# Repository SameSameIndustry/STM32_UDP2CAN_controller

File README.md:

# w5500_UDP — STM32G431 + W5500 UDP⇄CAN エンドエフェクタ制御基板

STM32G431 + WIZnet W5500(Ethernet) を使い、PC(Python)から UDP で直接 CAN バス上のアクチュエータ
(DJI C610 ESC / TTL サーボ / 差動ワイヤ機構モータ) を制御するための、基板設計(KiCad)・ファームウェア
(STM32CubeMX + CMake)・PC側ツール一式です。

## このリポジトリの範囲

ロボットアーム全体は「GIM6010/GIM8018 で関節を駆動する基板(192.168.1.100)」と「本基板=エンド
エフェクタ基板(192.168.1.101)」の 2 枚の STM32G431+W5500 基板を同一 LAN 上で使う構成を前提にしています。
**本リポジトリに含まれるファームウェアは 192.168.1.101 側(エンドエフェクタ基板)のみ**です。
GIM 基板側のファームウェアは別ファーム・別管理であり、ここには含まれていません
(`tools/odrive_setup/` の ODrive 初期設定スクリプトや `tools/hl_control/` 内の一部スクリプトは
GIM 側の調査・設定用に書かれたものですが、GIM 基板自体のファームウェアソースはありません)。

## ディレクトリ構成

| パス | 内容 |
|---|---|
| `UDP_w5500/` | KiCad 9 基板設計データ(回路図・PCB・ガーバー・3D モデル) |
| `UDP_w5500/jlcpcb/` | JLCPCB 発注用ガーバー・BOM・CPL(エクスポート済み) |
| `G431_w5500/` | STM32G431 ファームウェア本体(CMake ビルド) |
| `tools/as5600_monitor/` | AS5600 磁気エンコーダの角度を UDP 経由で監視する CLI |
| `tools/can_id_scanner/` | 2 基板分の状態を 1 ウィンドウ(上下2セクション)で見る Tkinter GUI、CAN ID 調査用スクリプト |
| `tools/hl_control/` | 高レベル制御 UDP プロトコルの実装・診断スクリプト、ROS2 連携 GUI |
| `tools/odrive_setup/` | ODrive ベースの GIM6010-8/GIM8108-8 を USB 経由で初期設定・較正するスクリプト(本基板のファームとは独立) |
| `CAN_PROTOCOL_*.md` | CAN バス上の各デバイスのフレーム仕様書 |
| `tools/hl_control/PROTOCOL_HL_CONTROL_UDP.md` | 高レベル制御 UDP プロトコル仕様書 |
| `ref/` | 使用部品(モータ・エンコーダ等)のデータシート・メーカー資料(参考資料) |
| `parts/` | KiCad 用の追加シンボル/フットプリント/3D モデルライブラリ |

## ハードウェア概要

- MCU: STM32G431CBT6 (Cortex-M4F)
- Ethernet: WIZnet **W5500**(SPI 接続、静的 IP)
- CAN: FDCAN1, **1 Mbps classic CAN**, 標準 11bit ID
- バス上のデバイスと CAN ID:

  | デバイス | CAN ID | 通信方向 | 仕様書 |
  |---|---|---|---|
  | DJI C610 (M2006 用 ESC) | `0x01`(ESC ID=1) + AS5600 フィードバック | 送受信 | — (DJI 標準プロトコル) |
  | TTL サーボ基板 | `0x21` | 受信専用(本基板からは送信しない) | [`CAN_PROTOCOL_TTL-SERVO.md`](CAN_PROTOCOL_TTL-SERVO.md) |
  | 差動ワイヤ機構モータ(ピッチ/ヨー) | `0x11` / `0x12` | 受信専用(本基板からは送信しない) | [`CAN_PROTOCOL_wave_motor.md`](CAN_PROTOCOL_wave_motor.md) |

- 3D モデル: `UDP_w5500/3D/UDP_w5500.step` が基板単体の統合 STEP。`3D_base*.ipt/.stl` /
  `3D_clear*.ipt/.stl` はエンクロージャ部品(Autodesk Inventor 形式 + 変換済み STL)。
  - 既知の注意点: PCB 上の RJ45 コネクタの 3D モデル参照(`${KIPRJMOD}/EASYEDA_MODELS/RJ45-TH_HR911105A.step`)
    は本リポジトリに含まれていません。KiCad の 3D ビューアでその部品だけ表示されませんが、
    回路設計・ガーバー出力には影響しません。

## ビルド環境

- [Arm GNU Toolchain](https://developer.arm.com/downloads/-/arm-gnu-toolchain-downloads)
  (`arm-none-eabi-gcc` 等) を PATH に追加
- CMake 3.22 以上、Ninja
- STM32CubeMX (`G431_w5500/G431_w5500.ioc` を編集・再生成する場合のみ)
- フラッシュ/デバッグ用に ST-Link デバッグプローブ + [OpenOCD](https://openocd.org/) 、
  または STM32CubeProgrammer

### CLI でビルド

```sh
cd G431_w5500
cmake --preset Debug
cmake --build --preset Debug
```

### VS Code でビルド/フラッシュ

本リポジトリには `.vscode/` 設定を同梱しています。

1. `.vscode/settings.json` の `cortex-debug.openocdPath`、`.vscode/tasks.json` の
   `Flash` タスクの `command` は `"openocd"` としてあります。OpenOCD を PATH に追加するか、
   お使いの環境のインストール先の絶対パスに書き換えてください。
2. `.vscode/c_cpp_properties.json` の `compilerPath` は Arm GNU Toolchain の Windows
   インストーラのデフォルト位置を指しています。インストール先が異なる場合は書き換えてください。
3. ビルド: `Ctrl+Shift+B` (`Build Debug` タスク、`cmake --build` を実行)
4. 書き込み: タスク `Flash` (`Build Debug` に依存、OpenOCD + ST-Link で書き込み・検証・リセット)
5. デバッグ: 実行とデバッグ → `Debug (OpenOCD)`

## ネットワーク設定(環境ごとに書き換えが必要)

基板の IP/MAC と、ブロードキャスト以外の送信先 PC の IP アドレスは
[`G431_w5500/Core/Src/main.c`](G431_w5500/Core/Src/main.c) 内にコンパイル時定数として直接
記述されています。**自分の環境の LAN 構成に合わせて書き換えてから書き込んでください。**

```c
.mac = {0x00, 0x08, 0xdc, 0x11, 0x22, 0x65},
.ip  = {192, 168, 1, 101},   // 本基板(エンドエフェクタ)の固定IP
.sn  = {255, 255, 255, 0},
.gw  = {192, 168, 1, 1},

uint8_t dest_ip[4] = {192, 168, 1, 2}; // ← PC側のIPアドレスに書き換える
```

GIM 基板(別ファーム)を同一 LAN に併設する場合は、IP(`192.168.1.100` 等)と MAC が重複しないように
してください。

### UDP ポート一覧

| ポート | 方向 | 用途 |
|---|---|---|
| 5000 | STM32→PC | 定期 "Hello" デモ送信(`dest_ip` 宛) |
| 5001 | PC↔STM32 | 生 CAN フレーム中継(CAN ID 調査・デバッグ用)。PC から 1 回何か送ると以後は受信した全 CAN フレームが転送される |
| 5002 | STM32→PC(broadcast) | ハートビート(定期送信、`255.255.255.255` 宛) |
| 5003 | PC→STM32(単方向) | 高レベル制御 UDP(TTL サーボ/wave motor/C610 を直接操作、詳細は [`PROTOCOL_HL_CONTROL_UDP.md`](tools/hl_control/PROTOCOL_HL_CONTROL_UDP.md)) |
| 5004 | STM32→PC | AS5600 角度モニタ(ストリーム配信) |
| 8888 | PC(ROS2)→STM32 | ROS2 連携プロトコル受信 |
| 8889 | STM32→PC(ROS2) | ROS2 連携プロトコル フィードバック送信 |

## PC 側ツール(Python)

Python 3.x、標準ライブラリ(`socket` / `struct` / `tkinter` / `argparse`)のみで動作します
(`tkinter` を使う GUI ツールは Tcl/Tk 入りの Python が必要)。`tools/odrive_setup/` の
スクリプトのみ追加で ODrive 公式ライブラリが必要です。

```sh
pip install odrive   # tools/odrive_setup/ のスクリプトを使う場合のみ
```

主なツール:

- `tools/can_id_scanner/can_id_scanner.py` — GIM 基板(100)とエンドエフェクタ基板(101)の
  両方を 1 ウィンドウ(上下2セクション)で扱う GUI。生 CAN フレーム(ポート5001)の送受信・デコード。
- `tools/hl_control/ros2_arm_control.py` — 同様の 2 基板 GUI(ROS2/sharmech プロトコル版、ポート8888/8889)。
- `tools/as5600_monitor/as5600_monitor.py` — AS5600 角度モニタ(ポート5004)の CLI クライアント。
- `tools/hl_control/diagnose_gim_axes.py` / `ramp_gim6010_pitch.py` — GIM 基板側の
  ODrive heartbeat 診断・角度ランプ送信(ポート5001 の生 CAN ブリッジ経由、GIM 基板向け)。
- `tools/odrive_setup/odrive_configure.py` / `odrive_inspect.py` 等 — USB 接続した
  ODrive(GIM6010-8/GIM8108-8)の初期設定・読み取り専用確認スクリプト。

いずれも `-h` / `--help` で使用法を確認できます。

## 基板発注

`UDP_w5500/jlcpcb/production_files/` に JLCPCB 向けの BOM・CPL・ガーバー一式(zip)が、
`UDP_w5500/jlcpcb/gerber/` に展開済みガーバー/ドリルデータがあります。他の基板製造業者を使う場合は
`UDP_w5500/UDP_w5500.kicad_pcb` から KiCad 9 でガーバーを再出力してください。

## 既知の制限・未解決事項

- RJ45 コネクタの 3D モデル参照が欠落している(上記参照)。電気的な設計・発注には影響しない。
- `tools/hl_control/ros2_arm_control.py` はワイヤフォーマットの仕様根拠として社内リポジトリ
  `sharmech`(非公開・本リポジトリには含まれない)の文書を参照しているコメントがありますが、
  スクリプト自体は標準ライブラリのみで完結しており、`sharmech` が無くても動作します。

## ライセンス

[MIT License](LICENSE)。ただし `G431_w5500/Core/Drivers/W5500/`(WIZnet ioLibrary)、
`G431_w5500/Drivers/CMSIS/`、`G431_w5500/Drivers/STM32G4xx_HAL_Driver/` は各ディレクトリ・
ファイルヘッダに記載された元のライセンス(WIZnet license / Apache-2.0 / BSD-3-Clause)に従います。

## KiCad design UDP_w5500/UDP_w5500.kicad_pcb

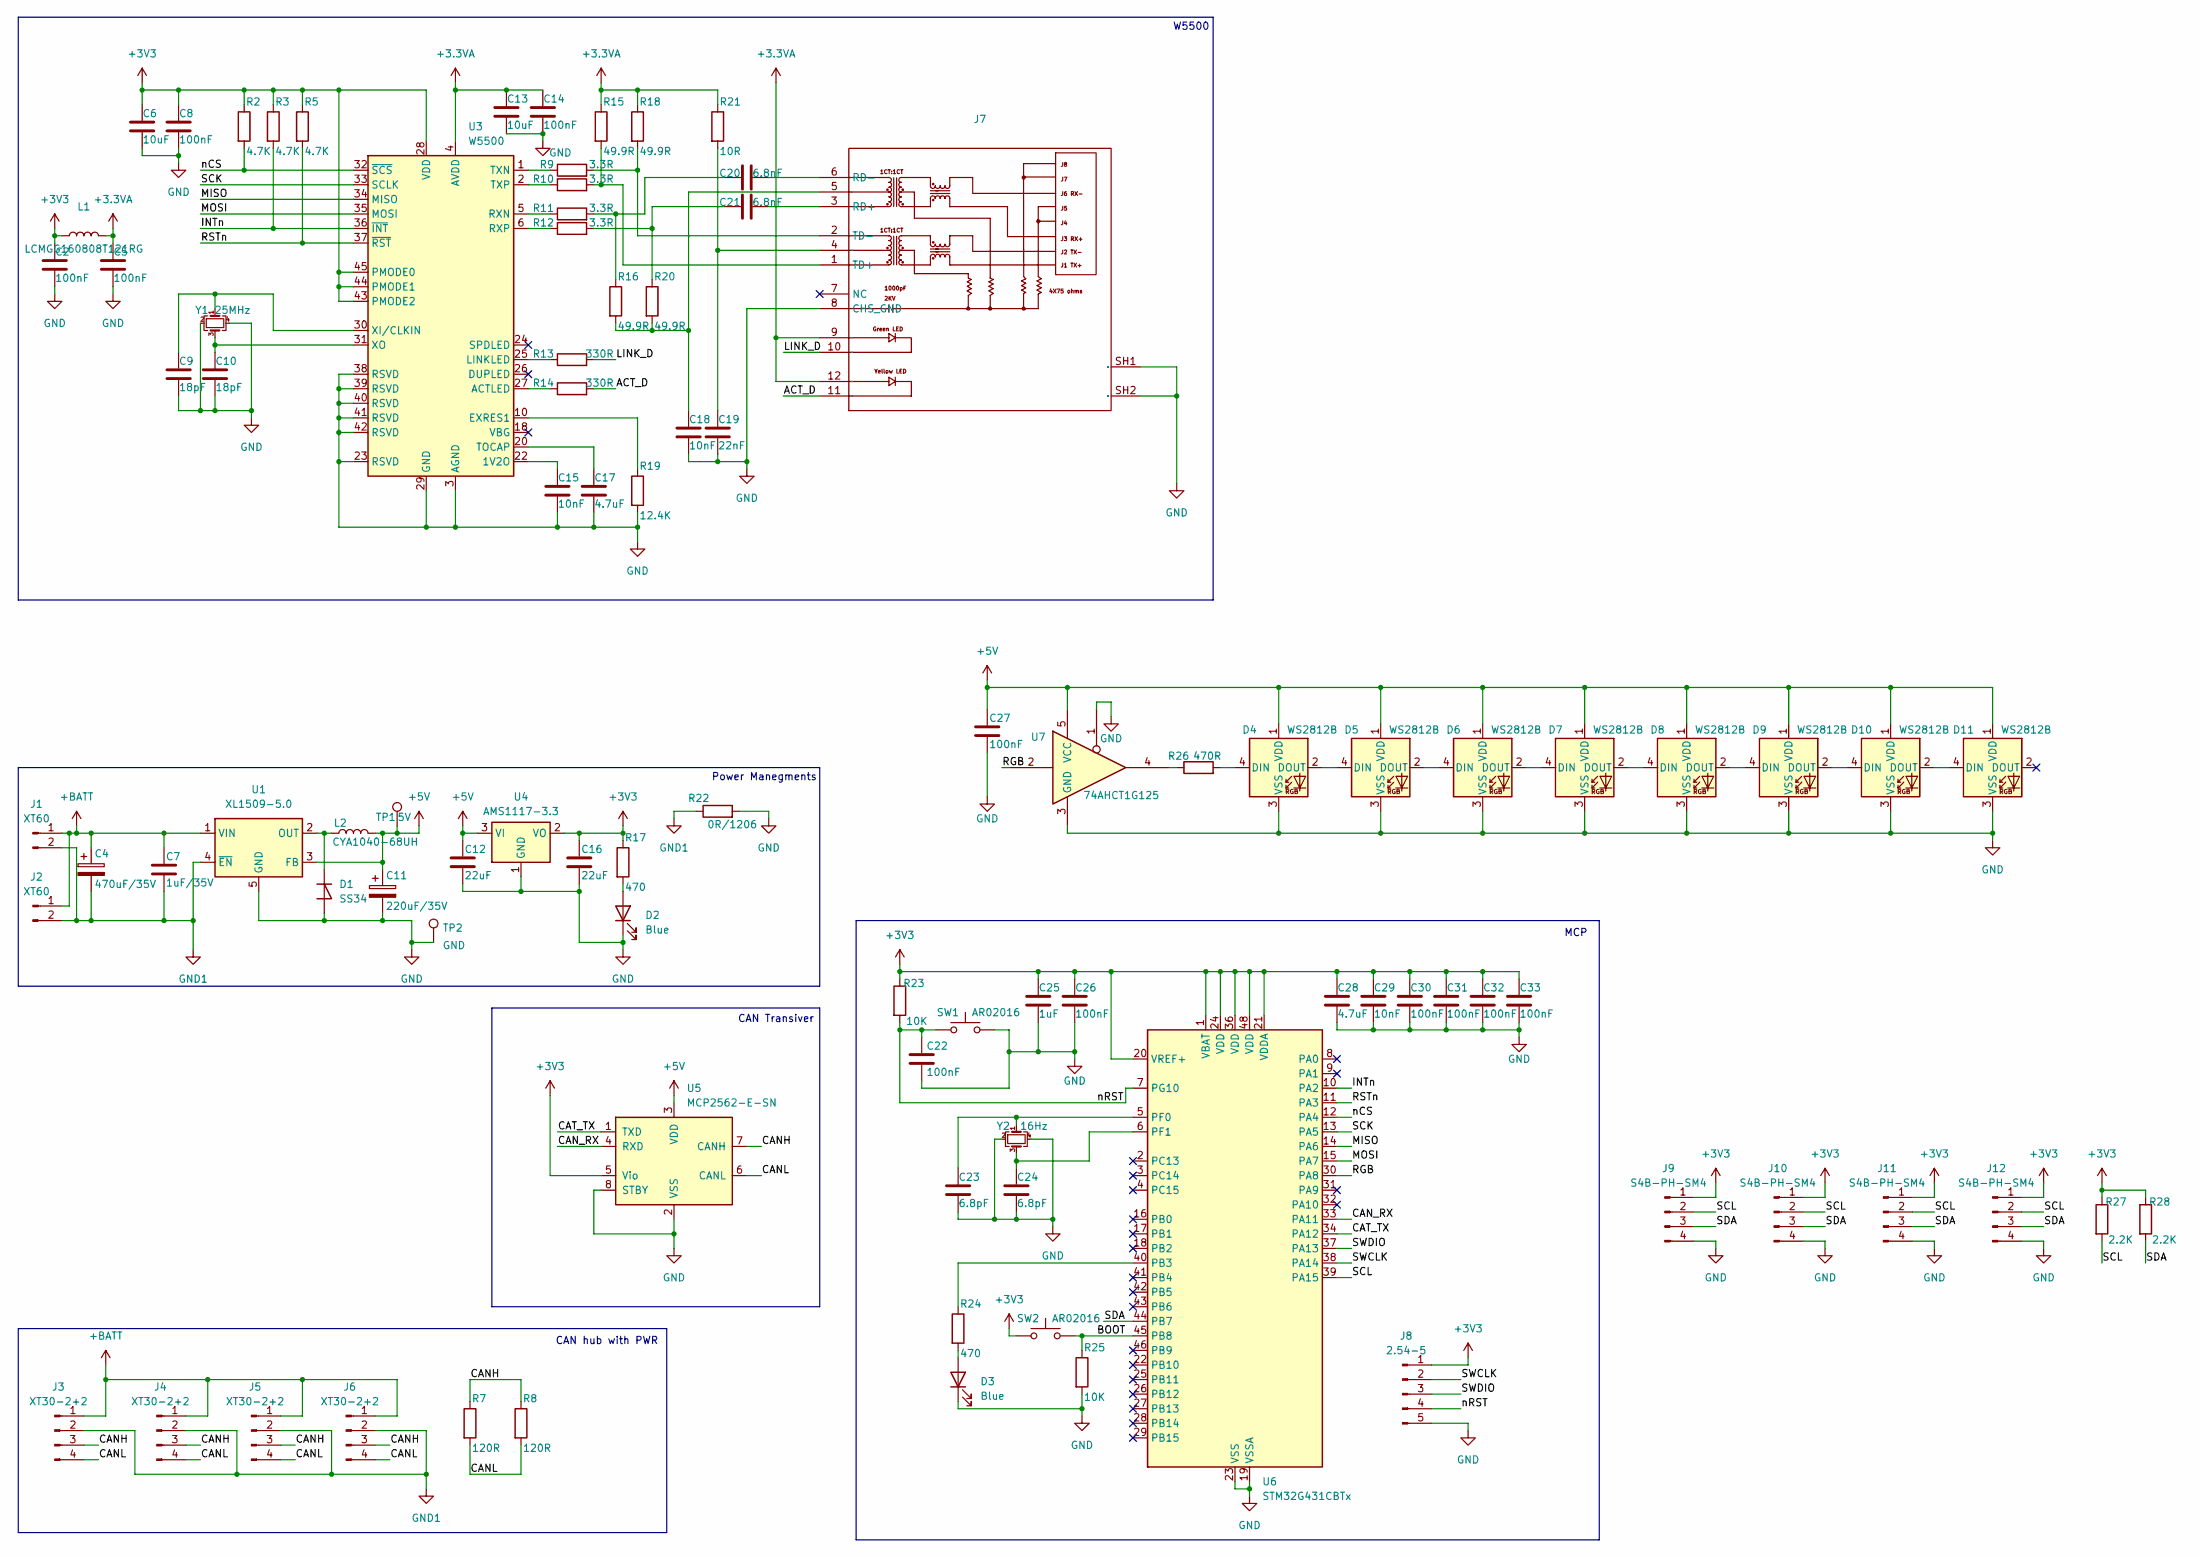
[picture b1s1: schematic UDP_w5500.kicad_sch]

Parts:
C2, C5, C8, C14, C22, C26, C27, C30, C31, C32, C33: 100nF; C_0603_1608Metric_Pad1.08x0.95mm_HandSolder; LCSC C14663
C4: 470uF/35V; CP_Radial_D10.0mm_P5.00mm
C6, C13: 10uF; C_0603_1608Metric_Pad1.08x0.95mm_HandSolder; LCSC C19702
C7: 1uF/35V; C_0603_1608Metric_Pad1.08x0.95mm_HandSolder; LCSC C15849
C9, C10: 18pF; C_0603_1608Metric_Pad1.08x0.95mm_HandSolder; LCSC C1647
C11: 220uF/35V; CP_Radial_D8.0mm_P3.50mm
C12, C16: 22uF; C_0603_1608Metric_Pad1.08x0.95mm_HandSolder; LCSC C59461
C15, C18, C29: 10nF; C_0603_1608Metric_Pad1.08x0.95mm_HandSolder; LCSC C57112
C17, C28: 4.7uF; C_0603_1608Metric_Pad1.08x0.95mm_HandSolder; LCSC C19666
C19: 22nF; C_0603_1608Metric_Pad1.08x0.95mm_HandSolder; LCSC C21122
C20, C21: 6.8nF; C_0603_1608Metric_Pad1.08x0.95mm_HandSolder; LCSC C1631
C23, C24: 6.8pF; C_0603_1608Metric_Pad1.08x0.95mm_HandSolder; LCSC C1679
C25: 1uF; C_0603_1608Metric_Pad1.08x0.95mm_HandSolder; LCSC C15849
D1: SS34; D_SMA; LCSC C8678
D2, D3: Blue; LED_0603_1608Metric_Pad1.05x0.95mm_HandSolder; LCSC C7012319
D4, D5, D6, D7, D8, D9, D10, D11: WS2812B; LED_WS2812B_PLCC4_5.0x5.0mm_P3.2mm
J1: XT60; AMASS_XT60IPW-M_1x03_P7.20mm_Horizontal
J2: XT60; AMASS_XT60PW-F_1x02_P7.20mm_Horizontal
J3, J4, J5, J6: XT30-2+2; CONN-TH_4P-XT30PW-M
J7: RJ45-TH_HR911105A; Manufacturer Part HR911105A; LCSC Part Name 弯插 带LED
J8: 2.54-5; PinHeader_1x05_P2.54mm_Vertical
J9, J10, J11, J12: S4B-PH-SM4; JST_PH_S4B-PH-SM4-TB_1x04-1MP_P2.00mm_Horizontal; LCSC C265102
L1: LCMGG160808T121RG; L_0603_1608Metric; LCSC C14709
L2: CYA1040-68UH; IND-SMD_L11.6-W10.1; LCSC C6364682
R2, R3, R5: 4.7K; R_0603_1608Metric_Pad0.98x0.95mm_HandSolder; LCSC C23162
R7, R8: 120R; R_0603_1608Metric_Pad0.98x0.95mm_HandSolder; LCSC C22787
R9, R10, R11, R12: 3.3R; R_0603_1608Metric_Pad0.98x0.95mm_HandSolder; LCSC C22979
R13, R14: 330R; R_0603_1608Metric_Pad0.98x0.95mm_HandSolder; LCSC C23138
R15, R16, R18, R20: 49.9R; R_0603_1608Metric_Pad0.98x0.95mm_HandSolder; LCSC C23185
R17, R24: 470; R_0603_1608Metric_Pad0.98x0.95mm_HandSolder; LCSC C23179
R19: 12.4K; R_0603_1608Metric_Pad0.98x0.95mm_HandSolder; LCSC C22865
R21: 10R; R_0603_1608Metric_Pad0.98x0.95mm_HandSolder; LCSC C22859
R22: 0R/1206; R_1206_3216Metric; LCSC C22356801
R23, R25: 10K; R_0603_1608Metric_Pad0.98x0.95mm_HandSolder; LCSC C25804
R26: 470R; R_0603_1608Metric_Pad0.98x0.95mm_HandSolder; LCSC C23179
R27, R28: 2.2K; R_0603_1608Metric_Pad0.98x0.95mm_HandSolder; LCSC C4190
SW1, SW2: AR02016; SW-SMD_L3.9-W3.0-P4.45; LCSC C720477
TP1: 5V; TestPoint_Pad_D3.0mm
TP2: GND; TestPoint_Pad_D3.0mm
U1: XL1509-5.0; SOIC-8_3.9x4.9mm_P1.27mm; LCSC C2902368
U3: W5500; LQFP-48_7x7mm_P0.5mm; LCSC C32843
U4: AMS1117-3.3; SOT-223-3_TabPin2; LCSC C6186
U5: MCP2562-E-SN; SOIC-8_3.9x4.9mm_P1.27mm; LCSC C53609
U6: STM32G431CBTx; LQFP-48_7x7mm_P0.5mm; LCSC C529355
U7: 74AHCT1G125; SOT-23-5_HandSoldering; LCSC C20617900
Y1: 25MHz; Crystal_SMD_3225-4Pin_3.2x2.5mm; LCSC C9006
Y2: 16Hz; Crystal_SMD_3225-4Pin_3.2x2.5mm; LCSC C13738

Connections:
+3.3VA: C5.1, C13.1, C14.1, J7.9, J7.12, L1.2, R15.1, R18.1, R21.1, U3.4 (AVDD), U3.8 (AVDD), U3.11 (AVDD), U3.15 (AVDD), U3.17 (AVDD), U3.21 (AVDD)
+3V3: C2.1, C6.1, C8.1, C16.1, C25.1, C26.1, C28.1, C29.1, C30.1, C31.1, C32.1, C33.1, J8.1, J9.1, J10.1, J11.1, J12.1, L1.1, R2.1, R3.1, R5.1, R17.1, R23.1, R27.1, R28.1, SW2.1, U3.28 (VDD), U3.43 (PMODE2), U3.44 (PMODE1), U3.45 (PMODE0), U4.2 (VO), U5.5 (Vio), U6.1 (VBAT), U6.20 (VREF+), U6.21 (VDDA), U6.24 (VDD), U6.36 (VDD), U6.48 (VDD)
+5V: C11.1, C12.1, C27.1, D4.1 (VDD), D5.1 (VDD), D6.1 (VDD), D7.1 (VDD), D8.1 (VDD), D9.1 (VDD), D10.1 (VDD), D11.1 (VDD), L2.2, TP1.1, U1.3 (FB), U4.3 (VI), U5.3 (VDD), U7.5 (VCC)
+BATT: C4.1, C7.1, J1.1, J2.1, J3.1, J4.1, J5.1, J6.1, U1.1 (VIN)
/ACT_D: J7.11, R14.2
/BOOT: R25.1, SW2.2, U6.45 (PB8)
/CANH: J3.3, J4.3, J5.3, J6.3, R7.1, R8.1, U5.7 (CANH)
/CANL: J3.4, J4.4, J5.4, J6.4, R7.2, R8.2, U5.6 (CANL)
/CAN_RX: U5.4 (RXD), U6.33 (PA11)
/CAT_TX: U5.1 (TXD), U6.34 (PA12)
/INTn: R3.2, U3.36 (~INT), U6.10 (PA2)
/LINK_D: J7.10, R13.2
/MISO: U3.34 (MISO), U6.14 (PA6)
/MOSI: U3.35 (MOSI), U6.15 (PA7)
/RGB: U6.30 (PA8), U7.2
/RSTn: R5.2, U3.37 (~RST), U6.11 (PA3)
/SCK: U3.33 (SCLK), U6.13 (PA5)
/SCL: J9.2, J10.2, J11.2, J12.2, R27.2, U6.39 (PA15)
/SDA: J9.3, J10.3, J11.3, J12.3, R28.2, U6.44 (PB7)
/SWCLK: J8.2, U6.38 (PA14)
/SWDIO: J8.3, U6.37 (PA13)
/nCS: R2.2, U3.32 (~SCS), U6.12 (PA4)
/nRST: C22.1, J8.4, R23.2, SW1.1, U6.7 (PG10)
GND: C2.2, C5.2, C6.2, C8.2, C9.2, C10.2, C11.2, C12.2, C13.2, C14.2, C15.2, C16.2, C17.2, C18.2, C19.2, C22.2, C23.2, C24.2, C25.2, C26.2, C27.2, C28.2, C29.2, C30.2, C31.2, C32.2, C33.2, D1.2 (A), D2.1 (K), D3.1 (K), D4.3 (VSS), D5.3 (VSS), D6.3 (VSS), D7.3 (VSS), D8.3 (VSS), D9.3 (VSS), D10.3 (VSS), D11.3 (VSS), J7.8 (CHS_GND), J7.SH1, J7.SH2, J8.5, J9.4, J10.4, J11.4, J12.4, R19.2, R22.2, R25.2, SW1.2, TP2.1, U1.5 (GND), U1.6 (GND), U1.7 (GND), U1.8 (GND), U3.3 (AGND), U3.9 (AGND), U3.14 (AGND), U3.16 (AGND), U3.19 (AGND), U3.23 (RSVD), U3.29 (GND), U3.38 (RSVD), U3.39 (RSVD), U3.40 (RSVD), U3.41 (RSVD), U3.42 (RSVD), U3.48 (AGND), U4.1 (GND), U5.2 (VSS), U5.8 (STBY), U6.19 (VSSA), U6.23 (VSS), U6.35 (VSS), U6.47 (VSS), U7.1, U7.3 (GND), Y1.2, Y1.4, Y2.2, Y2.4
GND1: C4.2, C7.2, J1.2, J2.2, J3.2, J4.2, J5.2, J6.2, R22.1, U1.4 (~EN)
unnamed: C18.1, J7.5, R16.2, R20.2
unnamed: C19.1, J7.4, R21.2
unnamed: C20.1, R11.2, R16.1
unnamed: C21.1, R12.2, R20.1
unnamed: D1.1 (K), L2.1, U1.2 (OUT)
unnamed: D2.2 (A), R17.2
unnamed: D3.2 (A), R24.2
unnamed: D4.4 (DIN), R26.2
unnamed: D4.2 (DOUT), D5.4 (DIN)
unnamed: D5.2 (DOUT), D6.4 (DIN)
unnamed: D6.2 (DOUT), D7.4 (DIN)
unnamed: D7.2 (DOUT), D8.4 (DIN)
unnamed: D8.2 (DOUT), D9.4 (DIN)
unnamed: D9.2 (DOUT), D10.4 (DIN)
unnamed: D10.2 (DOUT), D11.4 (DIN)
unnamed: C21.2, J7.3 (RD+)
unnamed: C20.2, J7.6 (RD-)
unnamed: J7.1 (TD+), R10.2, R15.2
unnamed: J7.2 (TD-), R9.2, R18.2
unnamed: R26.1, U7.4
unnamed: C15.1, U3.22 (1V2O)
unnamed: R14.1, U3.27 (ACTLED)
unnamed: R19.1, U3.10 (EXRES1)
unnamed: R13.1, U3.25 (LINKLED)
unnamed: R11.1, U3.5 (RXN)
unnamed: R12.1, U3.6 (RXP)
unnamed: C17.1, U3.20 (TOCAP)
unnamed: R9.1, U3.1 (TXN)
unnamed: R10.1, U3.2 (TXP)
unnamed: C9.1, U3.30 (XI/CLKIN), Y1.1
unnamed: C10.1, U3.31 (XO), Y1.3
unnamed: R24.1, U6.40 (PB3)
unnamed: C23.1, U6.5 (PF0), Y2.1
unnamed: C24.1, U6.6 (PF1), Y2.3

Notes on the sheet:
CAN hub with PWR
MCP
W5500
Power Manegments
CAN Transiver

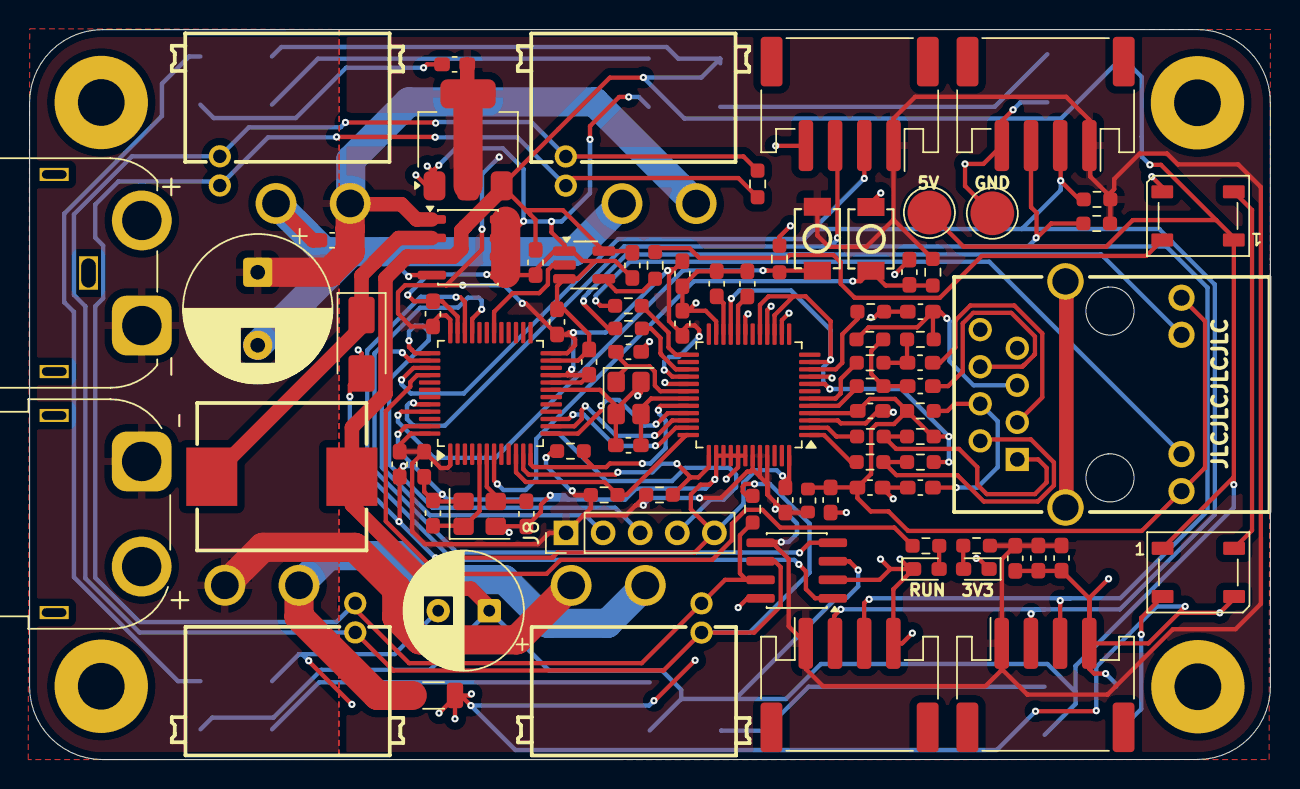
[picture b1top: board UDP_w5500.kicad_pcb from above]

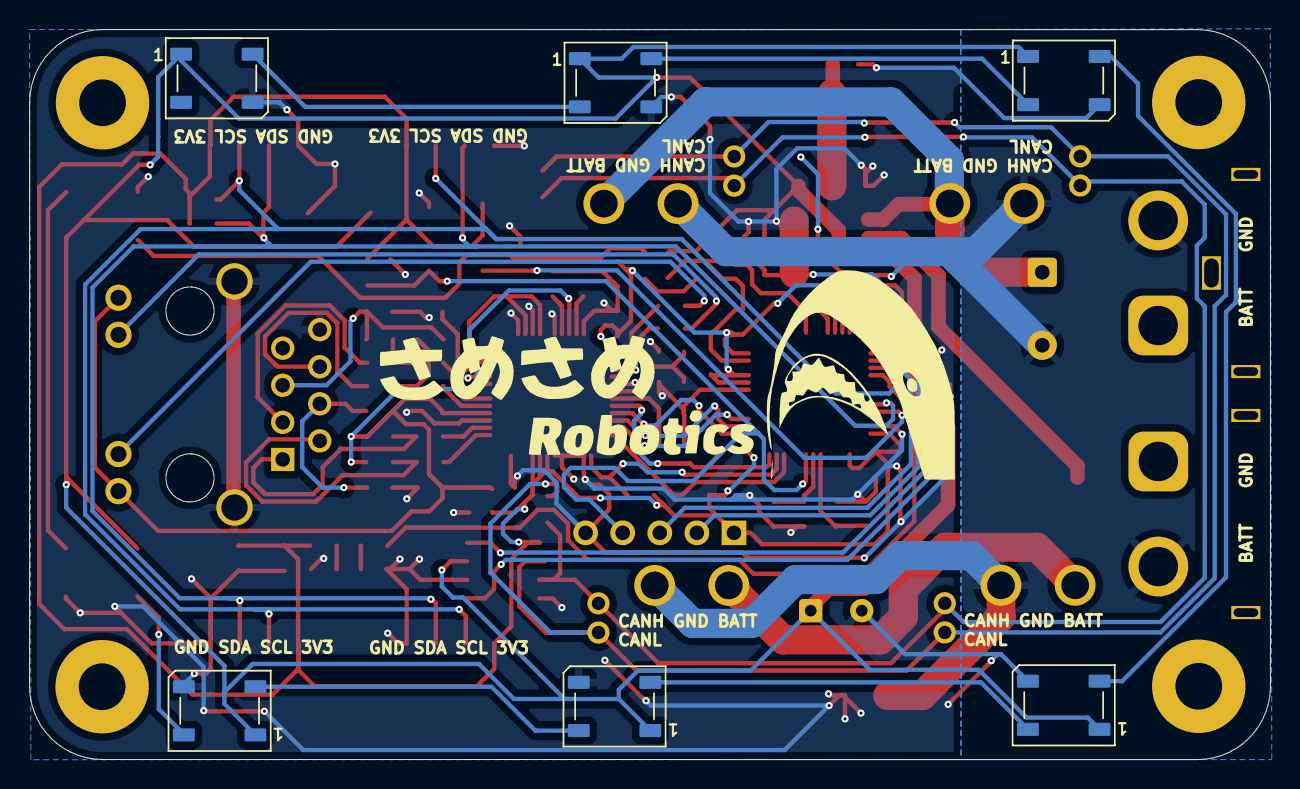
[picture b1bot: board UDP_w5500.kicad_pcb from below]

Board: 2 copper layers, 85.0 x 50.0 mm, 93 parts (6 on the bottom side), 59 nets.

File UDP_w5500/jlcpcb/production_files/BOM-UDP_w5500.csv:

Comment,Designator,Footprint,LCSC,Quantity
0R/1206,R22,R_1206_3216Metric,C22356801,1
100nF,"C14,C2,C22,C26,C27,C30,C31,C32,C33,C5,C8",C_0603_1608Metric_Pad1.08x0.95mm_HandSolder,C14663,11
10K,"R23,R25",R_0603_1608Metric_Pad0.98x0.95mm_HandSolder,C25804,2
10R,R21,R_0603_1608Metric_Pad0.98x0.95mm_HandSolder,C22859,1
10nF,"C15,C18,C29",C_0603_1608Metric_Pad1.08x0.95mm_HandSolder,C57112,3
10uF,"C13,C6",C_0603_1608Metric_Pad1.08x0.95mm_HandSolder,C19702,2
12.4K,R19,R_0603_1608Metric_Pad0.98x0.95mm_HandSolder,C22865,1
120R,"R7,R8",R_0603_1608Metric_Pad0.98x0.95mm_HandSolder,C22787,2
16Hz,Y2,Crystal_SMD_3225-4Pin_3.2x2.5mm,C13738,1
18pF,"C10,C9",C_0603_1608Metric_Pad1.08x0.95mm_HandSolder,C1647,2
1uF,C25,C_0603_1608Metric_Pad1.08x0.95mm_HandSolder,C15849,1
1uF/35V,C7,C_0603_1608Metric_Pad1.08x0.95mm_HandSolder,C15849,1
2.2K,"R27,R28",R_0603_1608Metric_Pad0.98x0.95mm_HandSolder,C4190,2
22nF,C19,C_0603_1608Metric_Pad1.08x0.95mm_HandSolder,C21122,1
22uF,"C12,C16",C_0603_1608Metric_Pad1.08x0.95mm_HandSolder,C59461,2
25MHz,Y1,Crystal_SMD_3225-4Pin_3.2x2.5mm,C9006,1
3.3R,"R10,R11,R12,R9",R_0603_1608Metric_Pad0.98x0.95mm_HandSolder,C22979,4
330R,"R13,R14",R_0603_1608Metric_Pad0.98x0.95mm_HandSolder,C23138,2
4.7K,"R2,R3,R5",R_0603_1608Metric_Pad0.98x0.95mm_HandSolder,C23162,3
4.7uF,"C17,C28",C_0603_1608Metric_Pad1.08x0.95mm_HandSolder,C19666,2
470,"R17,R24",R_0603_1608Metric_Pad0.98x0.95mm_HandSolder,C23179,2
470R,R26,R_0603_1608Metric_Pad0.98x0.95mm_HandSolder,C23179,1
49.9R,"R15,R16,R18,R20",R_0603_1608Metric_Pad0.98x0.95mm_HandSolder,C23185,4
6.8nF,"C20,C21",C_0603_1608Metric_Pad1.08x0.95mm_HandSolder,C1631,2
6.8pF,"C23,C24",C_0603_1608Metric_Pad1.08x0.95mm_HandSolder,C1679,2
74AHCT1G125,U7,SOT-23-5_HandSoldering,C20617900,1
AMS1117-3.3,U4,SOT-223-3_TabPin2,C6186,1
AR02016,"SW1,SW2",SW-SMD_L3.9-W3.0-P4.45,C720477,2
Blue,"D2,D3",LED_0603_1608Metric_Pad1.05x0.95mm_HandSolder,C7012319,2
CYA1040-68UH,L2,IND-SMD_L11.6-W10.1,C6364682,1
LCMGG160808T121RG,L1,L_0603_1608Metric,C14709,1
MCP2562-E-SN,U5,SOIC-8_3.9x4.9mm_P1.27mm,C53609,1
S4B-PH-SM4,"J10,J11,J12,J9",JST_PH_S4B-PH-SM4-TB_1x04-1MP_P2.00mm_Horizontal,C265102,4
SS34,D1,D_SMA,C8678,1
STM32G431CBTx,U6,LQFP-48_7x7mm_P0.5mm,C529355,1
W5500,U3,LQFP-48_7x7mm_P0.5mm,C32843,1
XL1509-5.0,U1,SOIC-8_3.9x4.9mm_P1.27mm,C2902368,1
XT30-2+2,J3,CONN-TH_4P-XT30PW-M,,1
XT60,J1,AMASS_XT60IPW-M_1x03_P7.20mm_Horizontal,,1
470uF/35V,C4,CP_Radial_D10.0mm_P5.00mm,,1
XT60,J2,AMASS_XT60PW-F_1x02_P7.20mm_Horizontal,,1
XT30-2+2,J4,CONN-TH_4P-XT30PW-M,,1
XT30-2+2,J5,CONN-TH_4P-XT30PW-M,,1
~,J7,RJ45-TH_HR911105A,,1
XT30-2+2,J6,CONN-TH_4P-XT30PW-M,,1
WS2812B,D4,LED_WS2812B_PLCC4_5.0x5.0mm_P3.2mm,,1
GND,TP2,TestPoint_Pad_D3.0mm,,1
2.54-5,J8,PinHeader_1x05_P2.54mm_Vertical,,1
5V,TP1,TestPoint_Pad_D3.0mm,,1
WS2812B,D5,LED_WS2812B_PLCC4_5.0x5.0mm_P3.2mm,,1
220uF/35V,C11,CP_Radial_D8.0mm_P3.50mm,,1
WS2812B,D8,LED_WS2812B_PLCC4_5.0x5.0mm_P3.2mm,,1
WS2812B,D11,LED_WS2812B_PLCC4_5.0x5.0mm_P3.2mm,,1
WS2812B,D6,LED_WS2812B_PLCC4_5.0x5.0mm_P3.2mm,,1
WS2812B,D9,LED_WS2812B_PLCC4_5.0x5.0mm_P3.2mm,,1
WS2812B,D10,LED_WS2812B_PLCC4_5.0x5.0mm_P3.2mm,,1
WS2812B,D7,LED_WS2812B_PLCC4_5.0x5.0mm_P3.2mm,,1

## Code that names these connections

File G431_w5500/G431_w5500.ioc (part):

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Mcu.Name=STM32G431C(6-8-B)Tx
Mcu.Package=LQFP48
Mcu.UserName=STM32G431CBTx
PA11.Mode=FDCAN_Activate
PA11.Signal=FDCAN1_RX
PA12.Mode=FDCAN_Activate
PA12.Signal=FDCAN1_TX
PA13.Mode=Serial_Wire
PA13.Signal=SYS_JTMS-SWDIO
PA14.Mode=Serial_Wire
PA14.Signal=SYS_JTCK-SWCLK
PA2.Signal=GPIO_Input
PA3.Signal=GPIO_Output
PA4.Signal=GPIO_Output
PA5.Mode=Full_Duplex_Master
PA5.Signal=SPI1_SCK
PA6.Mode=Full_Duplex_Master
PA6.Signal=SPI1_MISO
PA7.Mode=Full_Duplex_Master
PA7.Signal=SPI1_MOSI
PA8.Signal=S_TIM1_CH1
PB3.Signal=GPIO_Output
PF0-OSC_IN.Mode=HSE-External-Oscillator
PF0-OSC_IN.Signal=RCC_OSC_IN
PF1-OSC_OUT.Mode=HSE-External-Oscillator
PF1-OSC_OUT.Signal=RCC_OSC_OUT
RCC.HSE_VALUE=16000000
RCC.SYSCLKFreq_VALUE=48000000
RCC.SYSCLKSource=RCC_SYSCLKSOURCE_PLLCLK
board=custom

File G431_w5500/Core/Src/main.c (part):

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  // C610Current_Tick() が担当 (起動後2秒間は無送信)。
  HLControlUDP_SetC610(&c610_current, &c610_pos);

  // AS5600 磁気エンコーダ (ソフトウェアI2C: SCL=PA15, SDA=PB7)。
  // 角度は AS5600_StreamTick() が UDPポート5004へ周期送信する。
  AS5600_Init();

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  /*Configure GPIO pin Output Level */
  HAL_GPIO_WritePin(GPIOB, GPIO_PIN_3, GPIO_PIN_RESET);

  /*Configure GPIO pin : PA2 */
  GPIO_InitStruct.Pin = GPIO_PIN_2;
  GPIO_InitStruct.Mode = GPIO_MODE_INPUT;
  GPIO_InitStruct.Pull = GPIO_NOPULL;
  HAL_GPIO_Init(GPIOA, &GPIO_InitStruct);

  /*Configure GPIO pins : PA3 PA4 */
  GPIO_InitStruct.Pin = GPIO_PIN_3|GPIO_PIN_4;
  GPIO_InitStruct.Mode = GPIO_MODE_OUTPUT_PP;
  GPIO_InitStruct.Pull = GPIO_NOPULL;
  GPIO_InitStruct.Speed = GPIO_SPEED_FREQ_LOW;
  HAL_GPIO_Init(GPIOA, &GPIO_InitStruct);

  /*Configure GPIO pin : PB3 */
  GPIO_InitStruct.Pin = GPIO_PIN_3;
  GPIO_InitStruct.Mode = GPIO_MODE_OUTPUT_PP;
  GPIO_InitStruct.Pull = GPIO_NOPULL;
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

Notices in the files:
G431_w5500/Core/Src/main.c:
Copyright (c) 2026 STMicroelectronics.
All rights reserved.
This software is licensed under terms that can be found in the LICENSE file
